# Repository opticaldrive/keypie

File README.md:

# keypie
A custom RP2040 board with two USBC ports and two flash chips.
add magic sauce here

Can be used as a badUSB or to investigate USB connections(limited)

Firmware:
[https://circuitpython.org/board/raspberry_pi_pico/](https://circuitpython.org/board/raspberry_pi_pico/)

[https://github.com/earlephilhower/arduino-pico](https://github.com/earlephilhower/arduino-pico)

The second USBC port is made to work with RP2040's PIO using adafruit's tinyUSB libraries

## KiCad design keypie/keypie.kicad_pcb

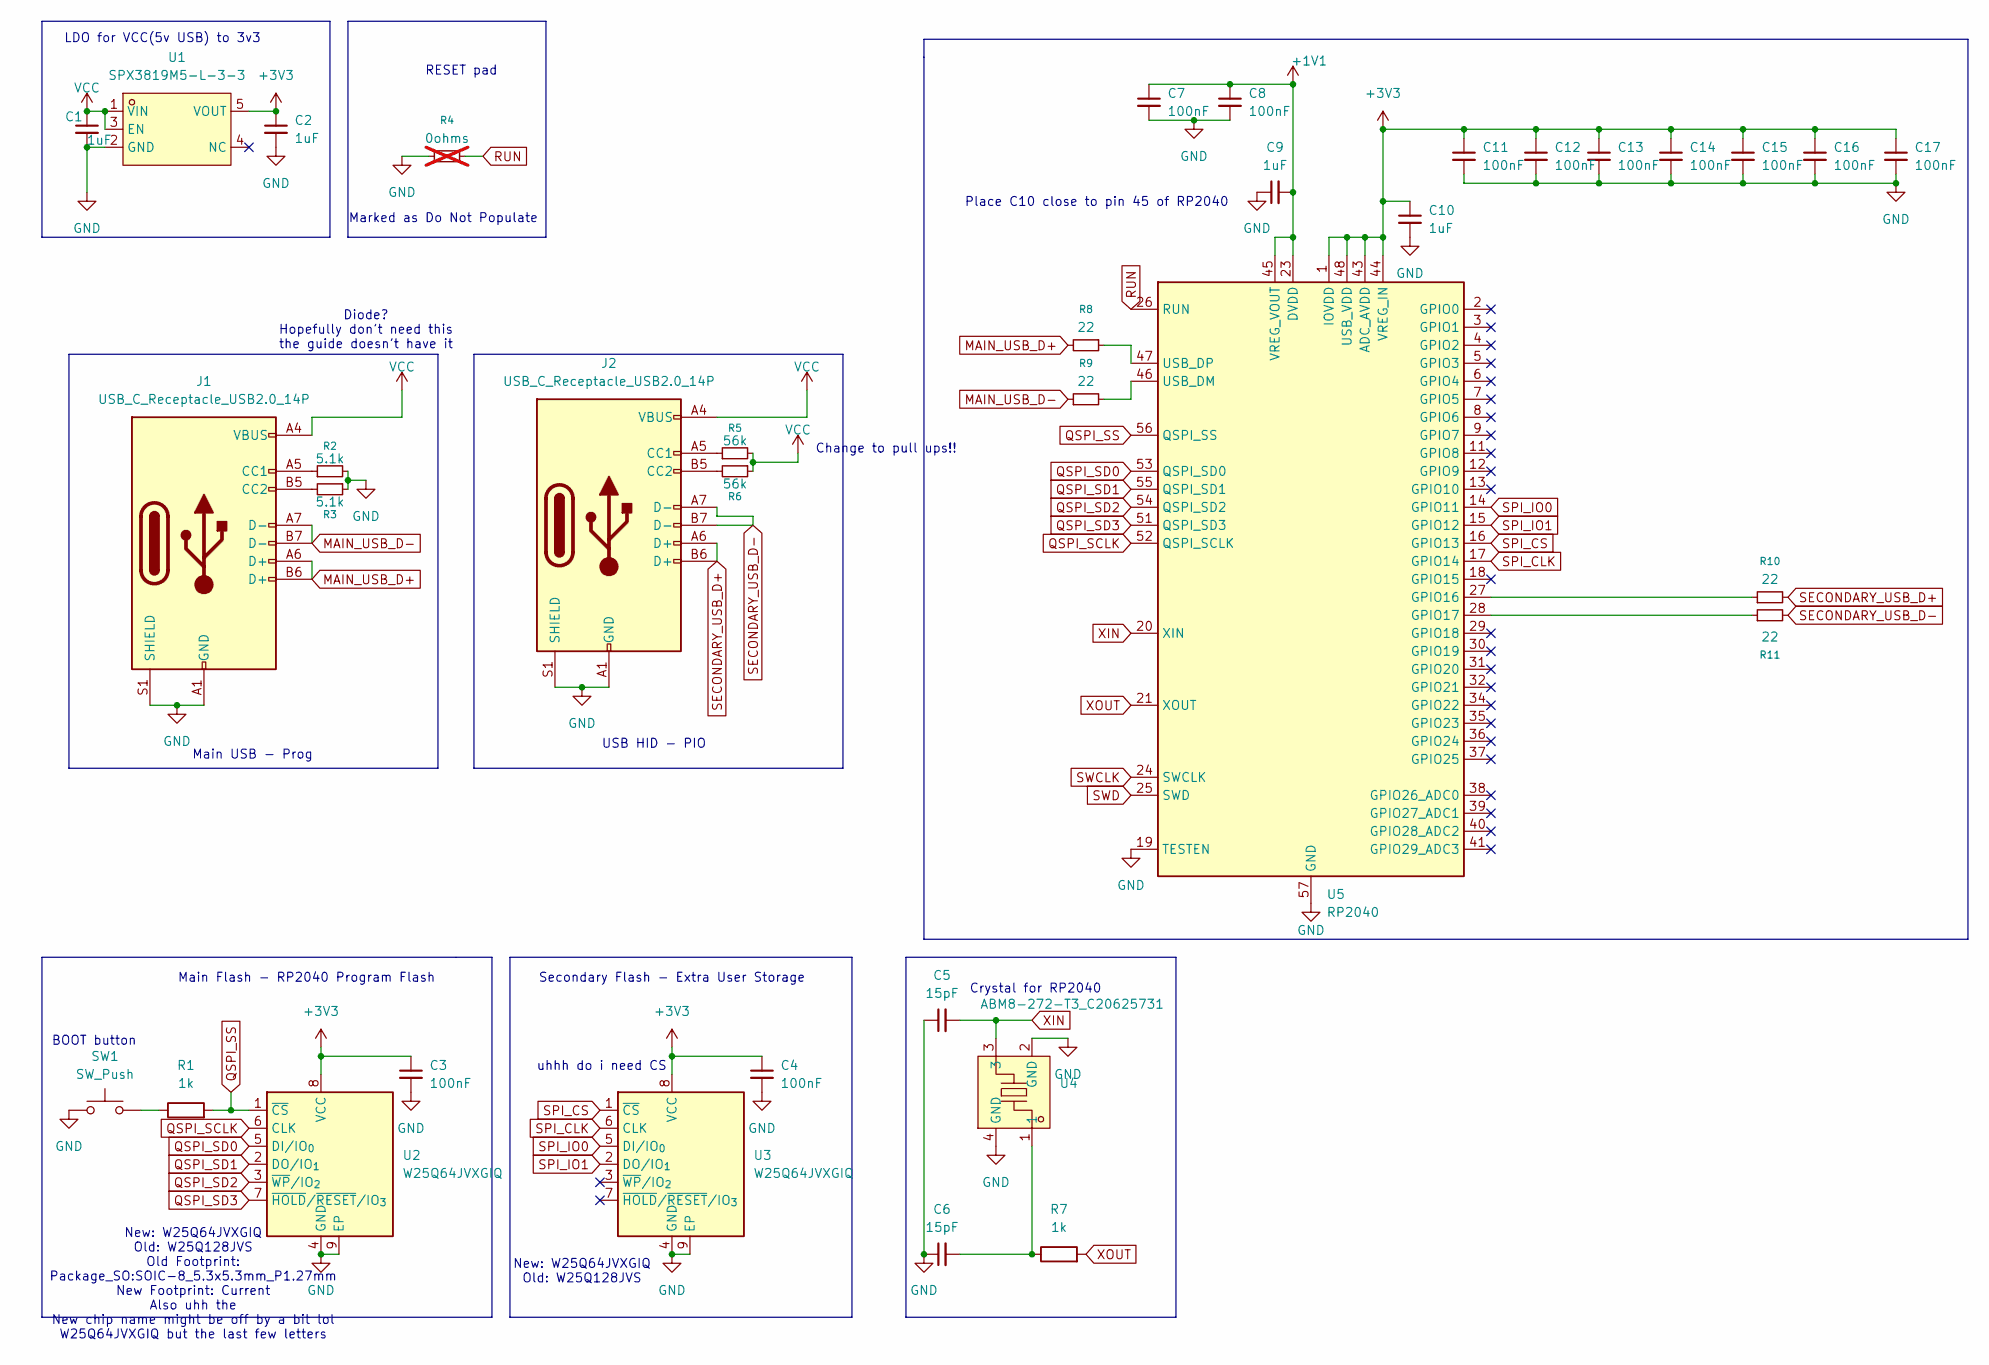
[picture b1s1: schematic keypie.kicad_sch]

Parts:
C1, C2, C9, C10: 1uF; C_0402_1005Metric
C3, C4, C7, C8, C11, C12, C13, C14, C15, C16, C17: 100nF; C_0402_1005Metric
C5, C6: 15pF; C_0402_1005Metric
J1, J2: USB_C_Receptacle_USB2.0_14P; USB_C_Receptacle_HRO_TYPE-C-31-M-12
R1, R7: 1k; C_0402_1005Metric
R2, R3: 5.1k; C_0402_1005Metric
R4: 0ohms; C_0402_1005Metric; not fitted
R5, R6: 56k; C_0402_1005Metric
R8, R9, R10, R11: 22; C_0402_1005Metric
SW1: SW_Push; SW-SMD_L3.9-W3.0-P4.45
U1: SPX3819M5-L-3-3; SOT-23-5_L3.0-W1.6-P0.95-LS2.8-BR; LCSC Part C20617301
U2, U3: W25Q64JVXGIQ; XSON-8_L4.0-W4.0-P0.80-TL-EP
U4: ABM8-272-T3_C20625731; CRYSTAL-SMD_4P-L3.2-W2.5-BL; LCSC Part C20625731
U5: RP2040; QFN-56-1EP_7x7mm_P0.4mm_EP3.2x3.2mm

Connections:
+1V1: C7.1, C8.1, C9.2, U5.23 (DVDD), U5.45 (VREG_VOUT), U5.50 (DVDD)
+3V3: C2.1, C3.1, C4.1, C10.1, C11.1, C12.1, C13.1, C14.1, C15.1, C16.1, C17.1, U1.5 (VOUT), U2.8 (VCC), U3.8 (VCC), U5.1 (IOVDD), U5.10 (IOVDD), U5.22 (IOVDD), U5.33 (IOVDD), U5.42 (IOVDD), U5.43 (ADC_AVDD), U5.44 (VREG_IN), U5.48 (USB_VDD), U5.49 (IOVDD)
GND: C1.2, C2.2, C3.2, C4.2, C5.1, C6.1, C7.2, C8.2, C9.1, C10.2, C11.2, C12.2, C13.2, C14.2, C15.2, C16.2, C17.2, J1.A1 (GND), J1.A12 (GND), J1.B1 (GND), J1.B12 (GND), J1.S1 (SHIELD), J2.A1 (GND), J2.A12 (GND), J2.B1 (GND), J2.B12 (GND), J2.S1 (SHIELD), R2.2, R3.1, R4.1, SW1.2, U1.2 (GND), U2.4 (GND), U2.9 (EP), U3.4 (GND), U3.9 (EP), U4.2 (GND), U4.4 (GND), U5.19 (TESTEN), U5.57 (GND)
MAIN_USB_D+: J1.A6 (D+), J1.B6 (D+), R8.2
MAIN_USB_D-: J1.A7 (D-), J1.B7 (D-), R9.1
unnamed: C6.2, R7.1, U4.1
unnamed: J1.A5 (CC1), R2.1
unnamed: J1.B5 (CC2), R3.2
unnamed: J2.A5 (CC1), R5.1
unnamed: J2.B5 (CC2), R6.2
unnamed: R1.1, SW1.1
unnamed: R10.1, U5.27 (GPIO16)
unnamed: R11.1, U5.28 (GPIO17)
unnamed: R9.2, U5.46 (USB_DM)
unnamed: R8.1, U5.47 (USB_DP)
QSPI_SCLK: U2.6 (CLK), U5.52 (QSPI_SCLK)
QSPI_SD0: U2.5 (DI/IO_{0}), U5.53 (QSPI_SD0)
QSPI_SD1: U2.2 (DO/IO_{1}), U5.55 (QSPI_SD1)
QSPI_SD2: U2.3 (~WP/IO_{2}), U5.54 (QSPI_SD2)
QSPI_SD3: U2.7 (~HOLD/~RESET/IO_{3}), U5.51 (QSPI_SD3)
QSPI_SS: R1.2, U2.1 (~CS), U5.56 (QSPI_SS)
RUN: R4.2, U5.26 (RUN)
SECONDARY_USB_D+: J2.A6 (D+), J2.B6 (D+), R10.2
SECONDARY_USB_D-: J2.A7 (D-), J2.B7 (D-), R11.2
SPI_CLK: U3.6 (CLK), U5.17 (GPIO14)
SPI_CS: U3.1 (~CS), U5.16 (GPIO13)
SPI_IO0: U3.5 (DI/IO_{0}), U5.14 (GPIO11)
SPI_IO1: U3.2 (DO/IO_{1}), U5.15 (GPIO12)
SWCLK: U5.24 (SWCLK)
SWD: U5.25 (SWD)
VCC: C1.1, J1.A4 (VBUS), J1.A9 (VBUS), J1.B4 (VBUS), J1.B9 (VBUS), J2.A4 (VBUS), J2.A9 (VBUS), J2.B4 (VBUS), J2.B9 (VBUS), R5.2, R6.1, U1.1 (VIN), U1.3 (EN)
XIN: C5.2, U4.3, U5.20 (XIN)
XOUT: R7.2, U5.21 (XOUT)

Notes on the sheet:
Main USB - Prog
USB HID - PIO
uhhh do i need CS
BOOT button
RESET pad
Place C10 close to pin 45 of RP2040
New: W25Q64JVXGIQ Old: W25Q128JVS
Main Flash - RP2040 Program Flash
Marked as Do Not Populate
LDO for VCC(5v USB) to 3v3
Crystal for RP2040
Diode? Hopefully don't need this the guide doesn't have it
Secondary Flash - Extra User Storage
New: W25Q64JVXGIQ Old: W25Q128JVS Old Footprint: Package_SO:SOIC-8_5.3x5.3mm_P1.27mm New Footprint: Current Also uhh the New chip name might be off by a bit lol W25Q64JVXGIQ but the last few letters
Change to pull ups!!

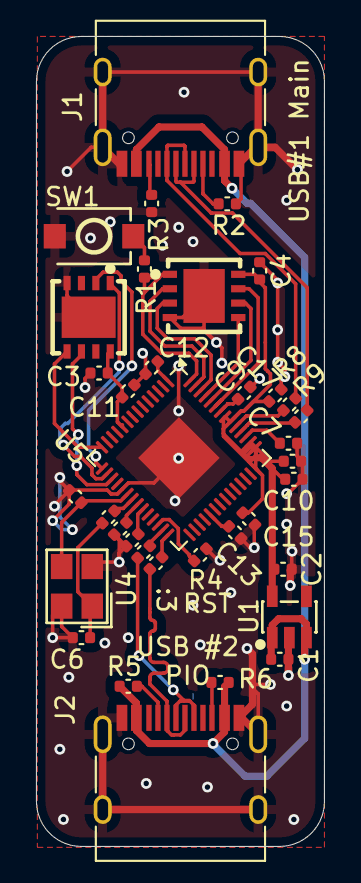
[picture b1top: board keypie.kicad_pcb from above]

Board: 2 copper layers, 16.0 x 45.0 mm, 36 parts (0 on the bottom side), 31 nets.

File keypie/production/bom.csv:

Designator,Footprint,Quantity,Value,LCSC Part #
"C1, C10, C2, C9",0402,4,1uF,
"C11, C12, C13, C14, C15, C16, C17, C3, C4, C7, C8",0402,11,100nF,
"C5, C6",0402,2,15pF,
"J1, J2",USB_C_Receptacle_HRO_TYPE-C-31-M-12,2,USB_C_Receptacle_USB2.0_14P,
"R1, R7",0402,2,1k,
"R10, R11, R8, R9",0402,4,22,
"R2, R3, R5, R6",0402,4,5.1k,
SW1,SW-SMD_L3.9-W3.0-P4.45,1,SW_Push,
U1,SOT-23-5_L3.0-W1.6-P0.95-LS2.8-BR,1,SPX3819M5-L-3-3,C20617301
"U2, U3",XSON-8_L4.0-W4.0-P0.80-TL-EP,2,W25Q64JVXGIQ,
U4,CRYSTAL-SMD_4P-L3.2-W2.5-BL,1,ABM8-272-T3_C20625731,C20625731
U5,QFN-56-1EP_7x7mm_P0.4mm_EP3.2x3.2mm,1,RP2040,

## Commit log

2025-07-18 aaa?
2025-07-18 aaaa?
2025-12-02 getting ready for prod
2025-12-02 here we go again
2025-12-02 bom and images
    bom and images
2025-12-02 aa
    aa
2026-01-10 better work or else
